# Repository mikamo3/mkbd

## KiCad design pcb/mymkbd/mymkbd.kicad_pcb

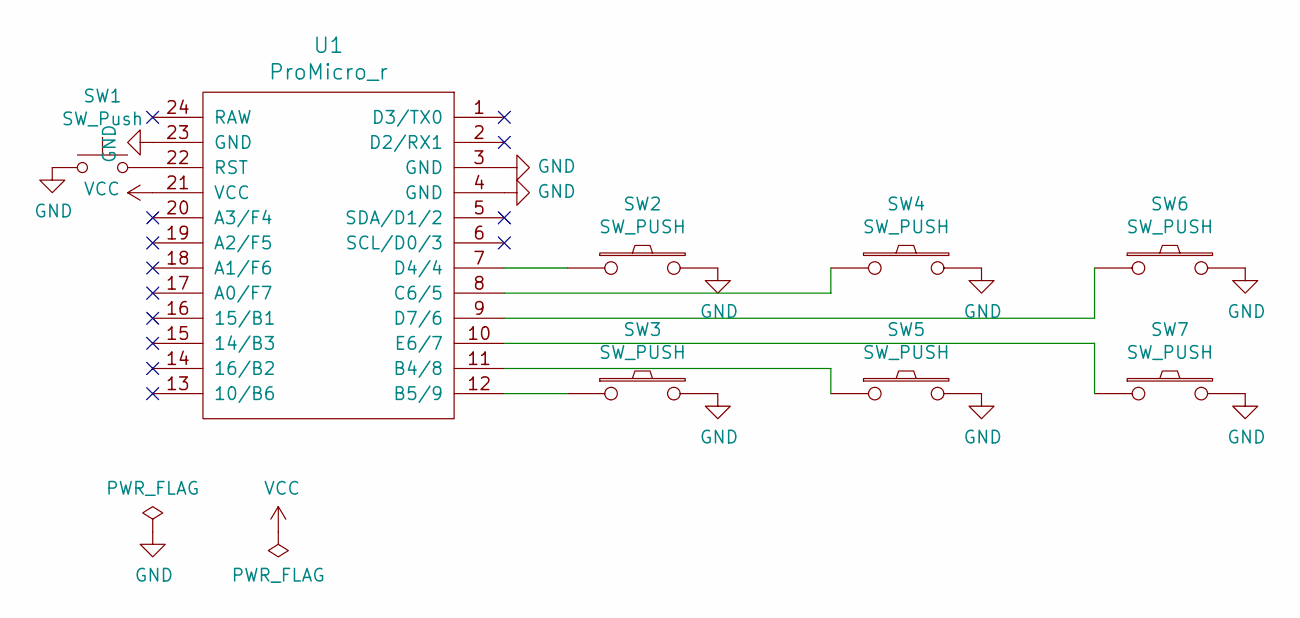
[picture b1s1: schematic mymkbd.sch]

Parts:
SW1: SW_Push; ResetSW_4
SW2, SW3, SW4, SW5, SW6, SW7: SW_PUSH; CherryMX_1u
U1: ProMicro_r; ProMicro_v3

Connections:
GND: SW1.1, SW2.2, SW3.2, SW4.2, SW5.2, SW6.2, SW7.2, U1.3 (GND), U1.4 (GND), U1.23 (GND)
unnamed: SW1.2, U1.22 (RST)
unnamed: SW2.1, U1.7 (D4/4)
unnamed: SW3.1, U1.12 (B5/9)
unnamed: SW4.1, U1.8 (C6/5)
unnamed: SW5.1, U1.11 (B4/8)
unnamed: SW6.1, U1.9 (D7/6)
unnamed: SW7.1, U1.10 (E6/7)
VCC: U1.21 (VCC)

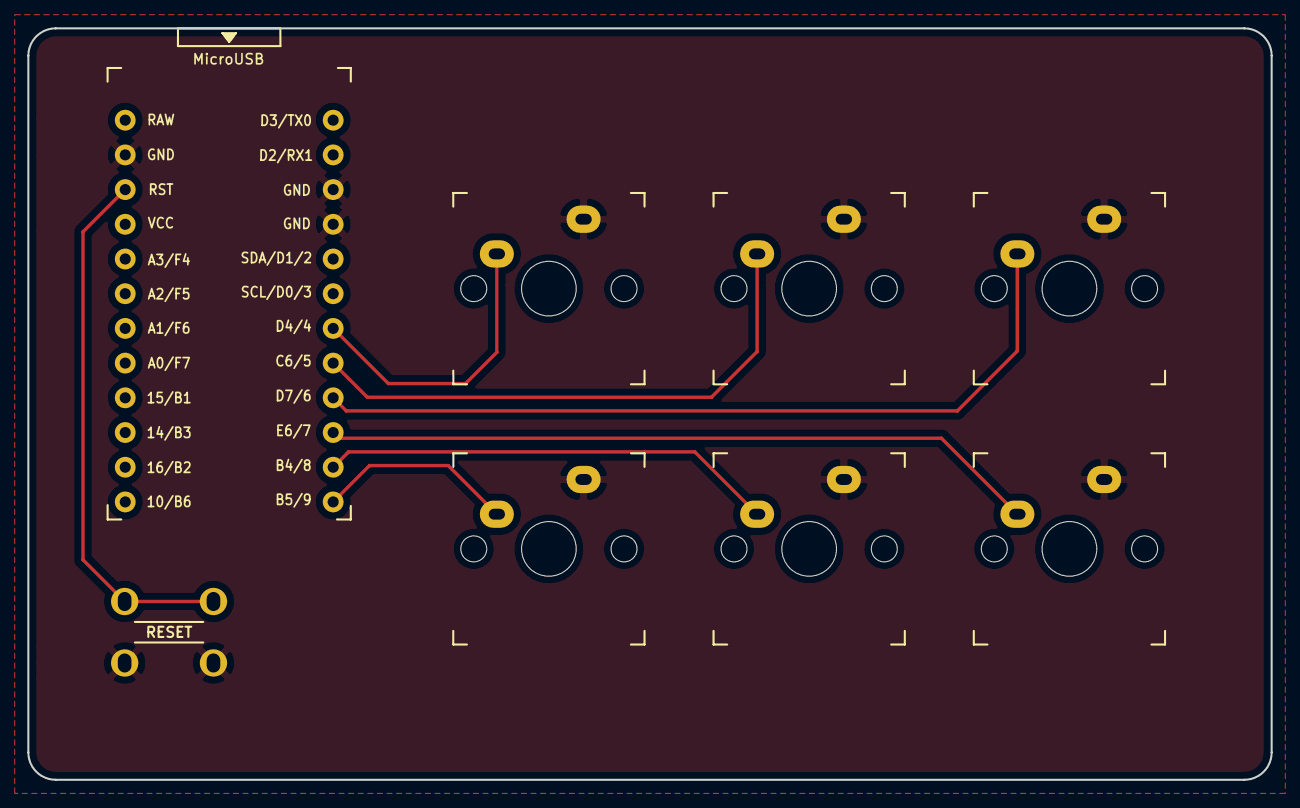
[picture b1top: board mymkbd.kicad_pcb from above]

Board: 2 copper layers, 91.0 x 55.0 mm, 8 parts (0 on the bottom side), 8 nets.

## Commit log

2020-06-13 create pcb
